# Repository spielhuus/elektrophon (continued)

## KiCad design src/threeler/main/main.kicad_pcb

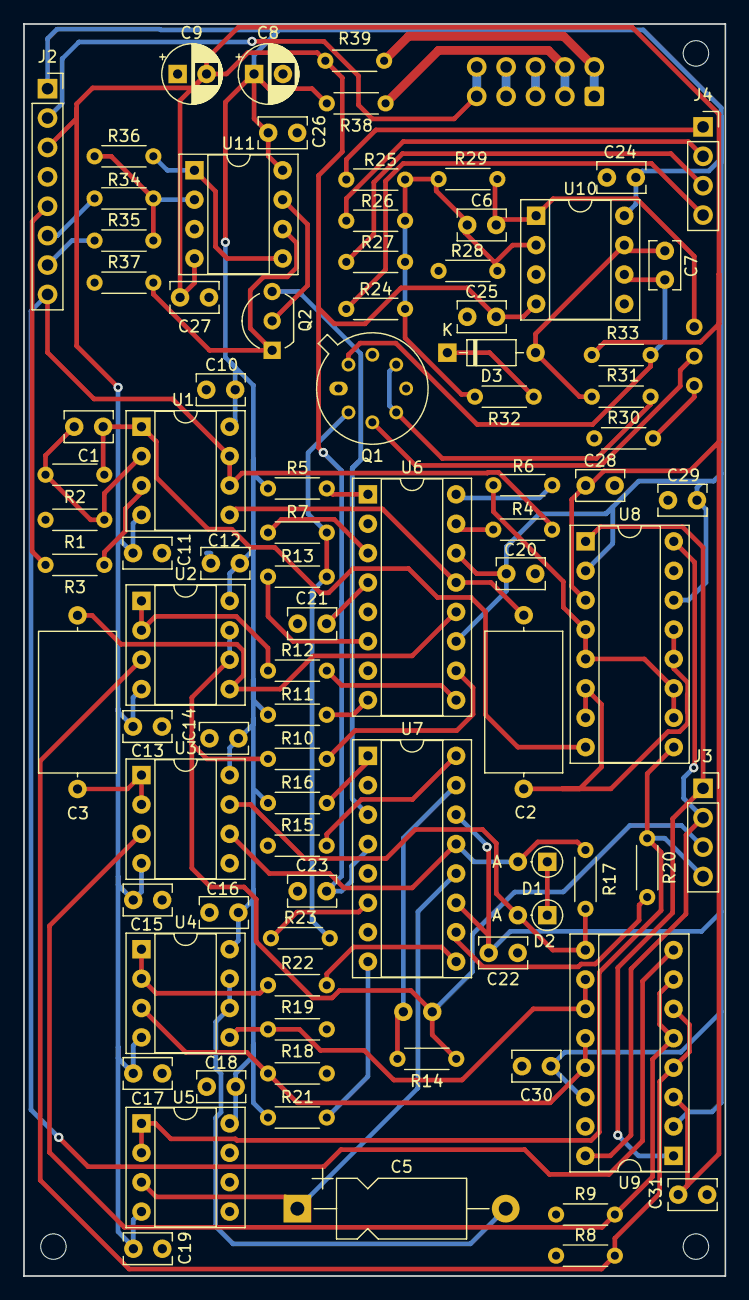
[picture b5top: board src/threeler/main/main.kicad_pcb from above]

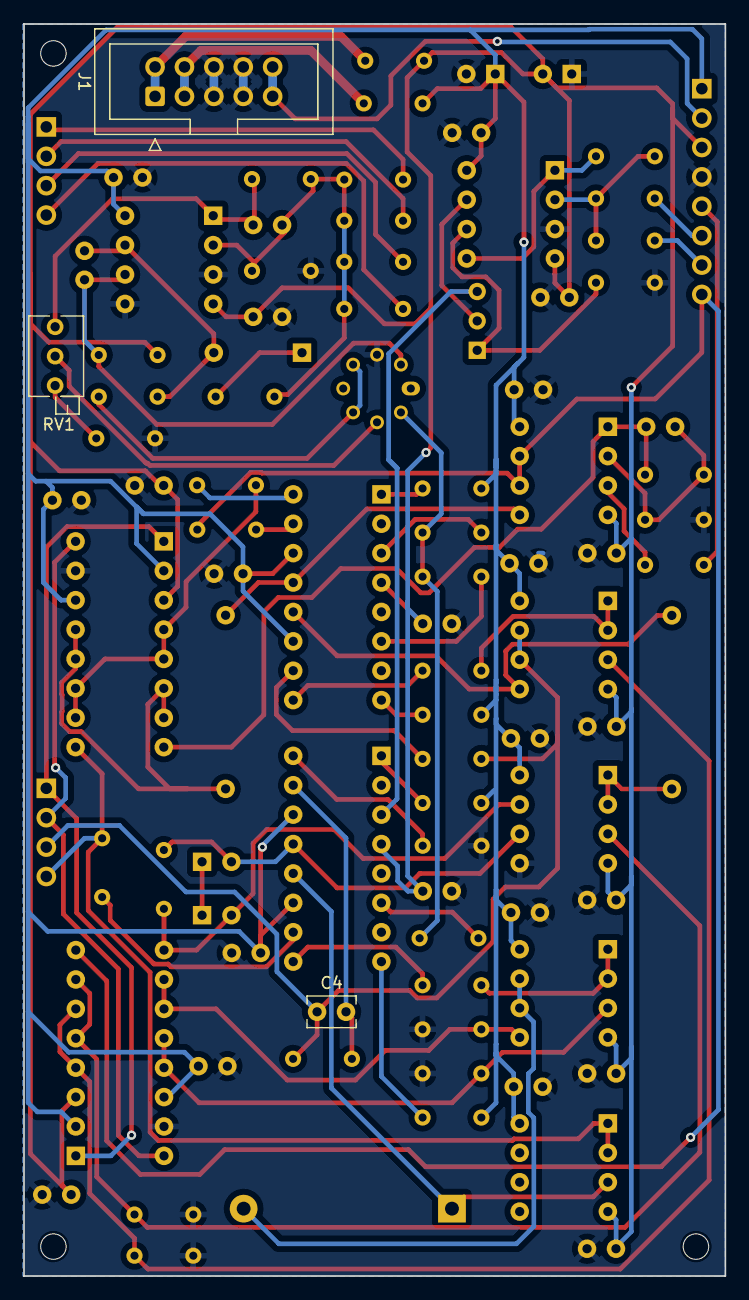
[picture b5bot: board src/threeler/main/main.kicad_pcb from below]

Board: 2 copper layers, 60.6 x 108.2 mm, 94 parts (3 on the bottom side), 66 nets.

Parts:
C1: 56p; C_Rect_L4.0mm_W2.5mm_P2.50mm
C2, C3: 220p; C_Axial_L12.0mm_D6.5mm_P15.00mm_Horizontal
C4: 470p; C_Rect_L4.0mm_W2.5mm_P2.50mm
C5: 220p; CP_Axial_L11.0mm_D5.0mm_P18.00mm_Horizontal
C6, C7: 180p; C_Rect_L4.0mm_W2.5mm_P2.50mm
C8, C9: 10u; CP_Radial_D5.0mm_P2.50mm
C10, C11, C12, C13, C14, C15, C16, C17, C18, C19, C20, C21, C22, C23, C24, C25, C26, C27, C28, C29, C30, C31: 100n; C_Rect_L4.0mm_W2.5mm_P2.50mm
D1, D2: 1N5236; D_DO-35_SOD27_P2.54mm_Vertical_AnodeUp
D3: 1N4148; D_DO-35_SOD27_P7.62mm_Horizontal
H2, H3, H4: MountingHole; MountingHole_2.2mm_M2
J1: IDC_Header; IDC-Header_2x05_P2.54mm_Vertical
J2: Connector; PinSocket_1x08_P2.54mm_Vertical
J3, J4: Connector; PinSocket_1x04_P2.54mm_Vertical
Q1: AS395; TO-5-8
Q2: 2N3906; TO-92_Inline_Wide
R1, R26, R36: 100k; R_Axial_DIN0204_L3.6mm_D1.6mm_P5.08mm_Horizontal
R2: 33k; R_Axial_DIN0204_L3.6mm_D1.6mm_P5.08mm_Horizontal
R3, R4, R6, R10, R12, R14, R15, R20, R22: 22k; R_Axial_DIN0204_L3.6mm_D1.6mm_P5.08mm_Horizontal
R5, R11, R16, R21: 68k; R_Axial_DIN0204_L3.6mm_D1.6mm_P5.08mm_Horizontal
R7, R13, R23, R37: 18k; R_Axial_DIN0204_L3.6mm_D1.6mm_P5.08mm_Horizontal
R8, R9, R18, R19: 5.6k; R_Axial_DIN0204_L3.6mm_D1.6mm_P5.08mm_Horizontal
R17: 220k; R_Axial_DIN0204_L3.6mm_D1.6mm_P5.08mm_Horizontal
R24, R34: 120k; R_Axial_DIN0204_L3.6mm_D1.6mm_P5.08mm_Horizontal
R25: 2.2meg; R_Axial_DIN0204_L3.6mm_D1.6mm_P5.08mm_Horizontal
R27: 150k; R_Axial_DIN0204_L3.6mm_D1.6mm_P5.08mm_Horizontal
R28: 270k; R_Axial_DIN0204_L3.6mm_D1.6mm_P5.08mm_Horizontal
R29: 2k; R_Axial_DIN0204_L3.6mm_D1.6mm_P5.08mm_Horizontal
R30: 330; R_Axial_DIN0204_L3.6mm_D1.6mm_P5.08mm_Horizontal
R31: 3.3k; R_Axial_DIN0204_L3.6mm_D1.6mm_P5.08mm_Horizontal
R32: 1meg; R_Axial_DIN0204_L3.6mm_D1.6mm_P5.08mm_Horizontal
R33: 330k; R_Axial_DIN0204_L3.6mm_D1.6mm_P5.08mm_Horizontal
R35: 100; R_Axial_DIN0204_L3.6mm_D1.6mm_P5.08mm_Horizontal
R38, R39: 10; R_Axial_DIN0204_L3.6mm_D1.6mm_P5.08mm_Horizontal
RV1: 100; Potentiometer_Bourns_3266Z_Horizontal
U1, U2, U3, U4, U5, U10, U11: OPA2134; DIP-8_W7.62mm_Socket
U6, U7: AS3280; DIP-16_W7.62mm_Socket
U8, U9: DG409; DIP-16_W7.62mm_Socket

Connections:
+5V: J1.9, J1.10, J2.2
+15V: C8.1, C10.1, C12.1, C14.1, C16.1, C18.1, C20.1, C22.1, C24.1, C26.1, C29.1, C30.1, J2.1, R5.2, R11.2, R16.2, R21.2, R38.2, U1.8 (V+), U2.8 (V+), U3.8 (V+), U4.8 (V+), U5.8 (V+), U6.11 (V+), U6.14 (V+), U7.11 (V+), U7.14 (V+), U8.2 (EN), U8.14, U9.2 (EN), U9.14, U10.8 (V+), U11.8 (V+)
-15V: C9.2, C11.2, C13.2, C15.2, C17.2, C19.2, C21.2, C23.2, C25.2, C27.2, C28.1, C31.1, J2.3, R33.2, R39.1, U1.4 (V-), U2.4 (V-), U3.4 (V-), U4.4 (V-), U5.4 (V-), U6.4 (V-), U7.4 (V-), U8.3, U9.3, U10.4 (V-), U11.4 (V-)
/A: Q1.2 (E), R7.2, R13.2, R23.2
/A0: J3.1, U8.1 (A0), U9.1 (A0)
/A1: J3.2, U8.16 (A1), U9.16 (A1)
/B: Q2.3 (C), U7.3
/COARSE: J4.4, R24.1
/FINE: J4.1, R25.2
/FM: J4.3, R27.2
/IN: J2.5, R3.2
/OUT_1: J2.8, R4.2, U1.6 (-), U1.7, U9.8
/OUT_2: C4.1, J3.3, R10.2, R14.1, U2.6 (-), U2.7
/OUT_3: J3.4, R20.1, U5.1, U5.2 (-), U8.9
/RES: J2.6, R34.1
/RES_MOD: J2.7, R35.2
/VN: J1.1, J1.2, R39.2
/VP: J1.3, J1.4, R38.1
/V/O: J4.2, R26.2
GND: C8.2, C9.1, C10.2, C11.1, C12.2, C13.1, C14.2, C15.1, C16.2, C17.1, C18.2, C19.1, C20.2, C21.1, C22.2, C23.1, C24.2, C25.1, C26.2, C27.1, C28.2, C29.2, C30.2, C31.2, J1.5, J1.6, J1.7, J1.8, J2.4, Q1.7 (B), R1.2, R8.2, R9.2, R15.2, R18.2, R19.2, R28.2, R30.2, R37.2, U3.5 (+), U8.15 (GND), U9.15 (GND), U10.3 (+), U10.5 (+), U11.3 (+)
unnamed: C1.1, R2.1, U1.1, U8.8
unnamed: C2.2, U8.6, U8.7, U8.12, U8.13
unnamed: C6.1, R29.1, RV1.1, U10.1
unnamed: D1.2 (A), R17.2, U3.6 (-), U7.13
unnamed: D1.1 (K), D2.1 (K)
unnamed: D2.2 (A), R17.1, U3.7, U9.9
unnamed: C7.2, D3.2 (A), R31.1, U10.7
unnamed: D3.1 (K), R32.1
unnamed: Q1.3 (B), RV1.2
unnamed: Q1.4 (C), Q1.6 (C), R31.2
unnamed: C7.1, Q1.8 (E), R33.1, U10.6 (-)
unnamed: Q2.2 (B), U11.7
unnamed: Q2.1 (E), R37.1, U11.6 (-)
unnamed: R6.1, U8.4, U8.5, U8.10, U8.11
unnamed: R7.1, U6.3
unnamed: R13.1, U6.6
unnamed: R23.1, U7.6
unnamed: R30.1, RV1.3
unnamed: R3.1, U1.3 (+)
unnamed: C1.2, R1.1, R2.2, U1.2 (-)
unnamed: C2.1, U1.5 (+), U6.13
unnamed: R8.1, U2.3 (+), U9.4, U9.6
unnamed: R12.1, U2.1, U2.2 (-)
unnamed: C3.1, U2.5 (+), U6.12
unnamed: R9.1, U3.3 (+), U9.5, U9.7
unnamed: C3.2, U3.1, U3.2 (-)
unnamed: R18.1, U4.3 (+), U9.12, U9.13
unnamed: R22.1, U4.1, U4.2 (-)
unnamed: R19.1, U4.5 (+), U9.10, U9.11
unnamed: C5.2, U4.6 (-), U4.7
unnamed: C5.1, U5.3 (+), U7.12
unnamed: R6.2, U6.16 (+)
unnamed: R4.1, U6.15 (-)
unnamed: R5.1, U6.1 (ID)
unnamed: R12.2, U6.9 (+)
unnamed: R10.1, U6.10 (-)
unnamed: R11.1, U6.8 (ID)
unnamed: R15.1, U7.16 (+)
unnamed: C4.2, R14.2, U7.15 (-)
unnamed: R16.1, U7.1 (ID)
unnamed: R22.2, U7.9 (+)
unnamed: R20.2, U7.10 (-)
unnamed: R21.1, U7.8 (ID)
unnamed: C6.2, R24.2, R25.1, R26.1, R27.1, R28.1, R29.2, R32.2, U10.2 (-)
unnamed: R34.2, R35.1, R36.2, U11.2 (-)
unnamed: R36.1, U11.1, U11.5 (+)

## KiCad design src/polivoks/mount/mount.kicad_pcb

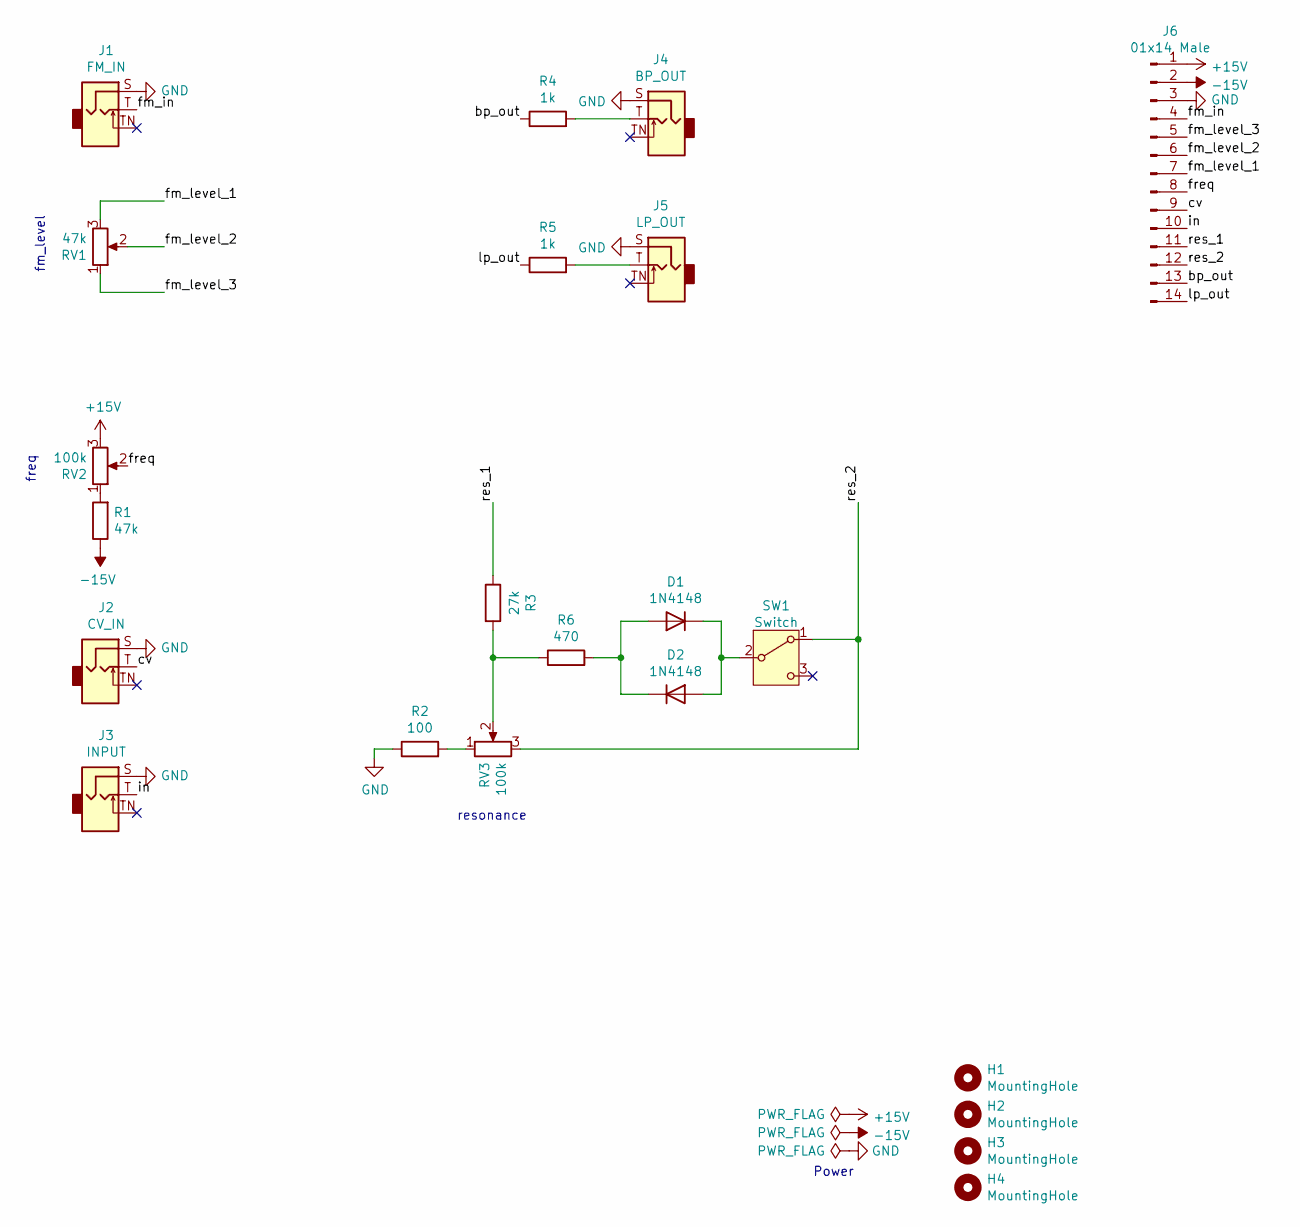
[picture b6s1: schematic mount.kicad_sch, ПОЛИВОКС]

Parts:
D1, D2: 1N4148; D_DO-35_SOD27_P7.62mm_Horizontal
H1, H2, H3, H4: MountingHole; MountingHole_2.2mm_M2
J1: FM_IN; Jack_3.5mm_WQP-PJ398SM_Vertical
J2: CV_IN; Jack_3.5mm_WQP-PJ398SM_Vertical
J3: INPUT; Jack_3.5mm_WQP-PJ398SM_Vertical
J4: BP_OUT; Jack_3.5mm_WQP-PJ398SM_Vertical
J5: LP_OUT; Jack_3.5mm_WQP-PJ398SM_Vertical
J6: 01x14 Male; PinHeader_1x14_P2.54mm_Vertical
R1: 47k; R_Axial_DIN0207_L6.3mm_D2.5mm_P10.16mm_Horizontal
R2: 100; R_Axial_DIN0207_L6.3mm_D2.5mm_P10.16mm_Horizontal
R3: 27k; R_Axial_DIN0207_L6.3mm_D2.5mm_P10.16mm_Horizontal
R4, R5: 1k; R_Axial_DIN0207_L6.3mm_D2.5mm_P10.16mm_Horizontal
R6: 470; R_Axial_DIN0207_L6.3mm_D2.5mm_P10.16mm_Horizontal
RV1: 47k; Potentiometer_Alpha_RD901F-40-00D_Single_Vertical
RV2, RV3: 100k; Potentiometer_Alpha_RD901F-40-00D_Single_Vertical
SW1: Switch; SPDT_KIT

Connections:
+15V: J6.1, RV2.3
-15V: J6.2, R1.1
/bp_out: J6.13, R4.1
/cv: J2.T, J6.9
/fm_in: J1.T, J6.4
/fm_level_1: J6.7, RV1.3
/fm_level_2: J6.6, RV1.2
/fm_level_3: J6.5, RV1.1
/freq: J6.8, RV2.2
/in: J3.T, J6.10
/lp_out: J6.14, R5.1
/res_1: J6.11, R3.1
/res_2: J6.12, RV3.3, SW1.1 (A)
GND: J1.S, J2.S, J3.S, J4.S, J5.S, J6.3, R2.1
unnamed: D1.2 (A), D2.1 (K), R6.2
unnamed: D1.1 (K), D2.2 (A), SW1.2 (B)
unnamed: J4.T, R4.2
unnamed: J5.T, R5.2
unnamed: R1.2, RV2.1
unnamed: R2.2, RV3.1
unnamed: R3.2, R6.1, RV3.2

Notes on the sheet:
fm_level
Power
freq
resonance

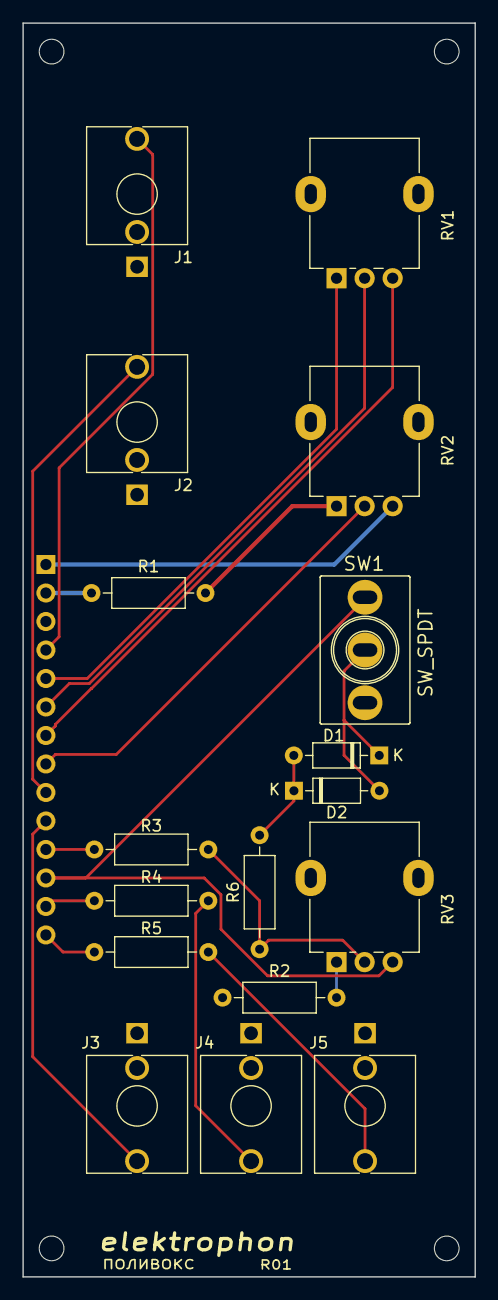
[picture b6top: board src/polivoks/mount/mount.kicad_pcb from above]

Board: 2 copper layers, 40.3 x 111.8 mm, 22 parts (1 on the bottom side), 21 nets.

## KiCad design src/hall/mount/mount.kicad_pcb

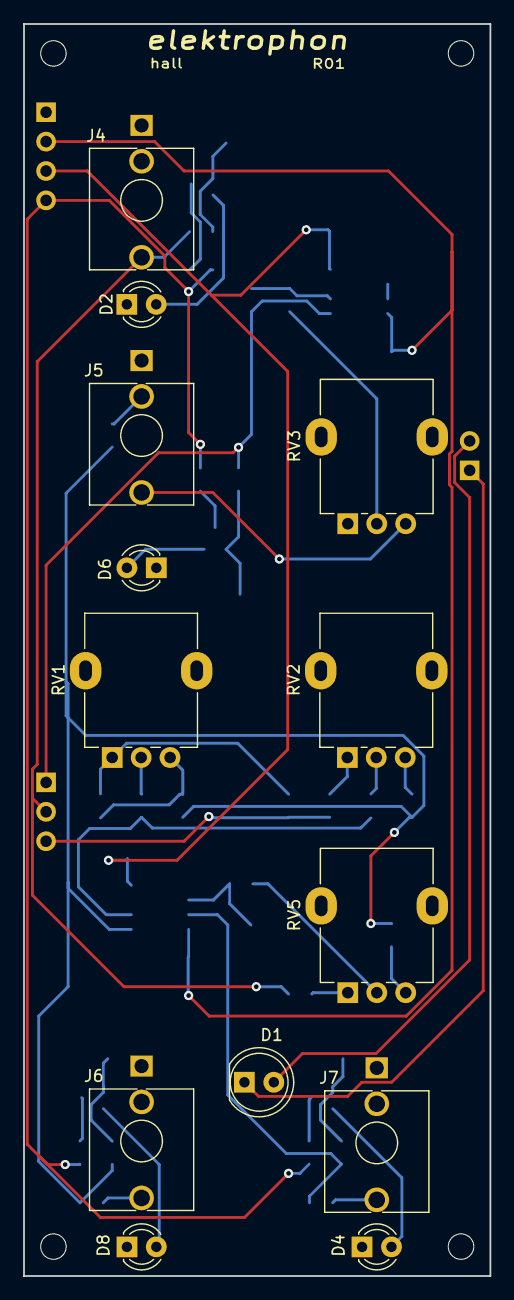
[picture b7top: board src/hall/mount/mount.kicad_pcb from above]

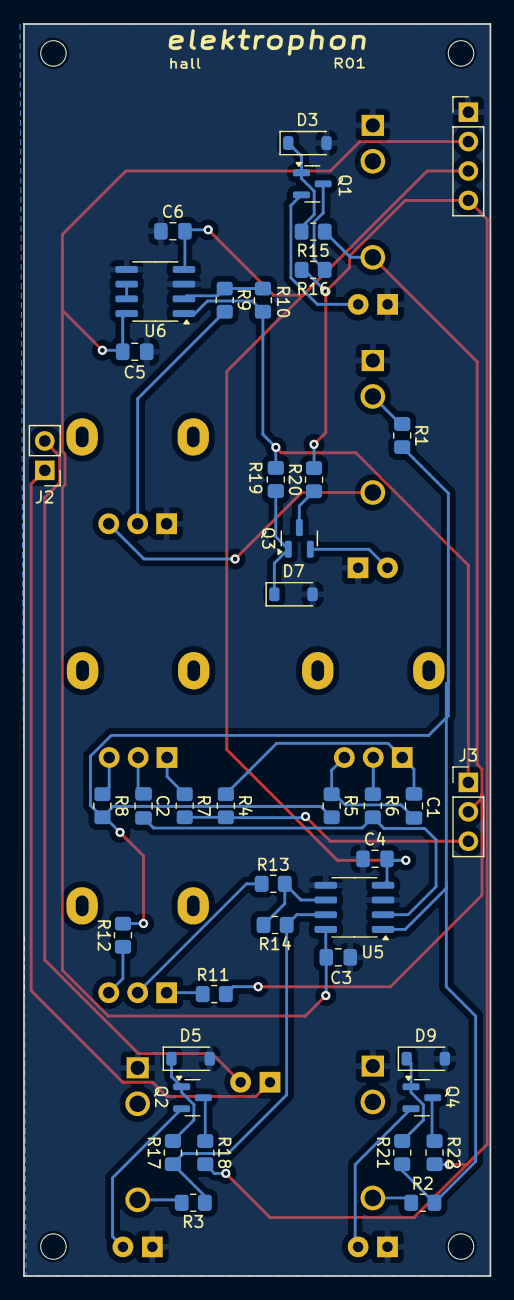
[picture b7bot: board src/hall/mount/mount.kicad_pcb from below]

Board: 2 copper layers, 40.3 x 108.2 mm, 58 parts (41 on the bottom side), 41 nets.

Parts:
C1: 47n (C0G); C_0805_2012Metric_Pad1.18x1.45mm_HandSolder
C2: 560p (C0G); C_0805_2012Metric_Pad1.18x1.45mm_HandSolder
C3, C4, C5, C6: 100n; C_0805_2012Metric_Pad1.18x1.45mm_HandSolder
D1: LED (Red); LED_D5.0mm
D2, D6: LED (Green); LED_D3.0mm
D3, D5, D7, D9: 1N4148W; D_SOD-123
D4, D8: LED (Red); LED_D3.0mm
H1: H1; MountingHole_2.2mm_M2
H2: H2; MountingHole_2.2mm_M2
H3: H3; MountingHole_2.2mm_M2
H4: H4; MountingHole_2.2mm_M2
J1: 01x04 Male; PinHeader_1x04_P2.54mm_Vertical
J2: 01x02 Male; PinHeader_1x02_P2.54mm_Vertical
J3: 01x03 Male; PinHeader_1x03_P2.54mm_Vertical
J4, J5, J6, J7: PJ398SM; Jack_3.5mm_WQP-PJ398SM_Vertical
Q1, Q2, Q3, Q4: MMBT3904; SOT-23
R1, R2, R3: 1k; R_0805_2012Metric_Pad1.20x1.40mm_HandSolder
R4, R5, R6: 22k; R_0805_2012Metric_Pad1.20x1.40mm_HandSolder
R7, R8, R11, R12: 10k; R_0805_2012Metric_Pad1.20x1.40mm_HandSolder
R9, R10, R13, R14, R15, R17, R19, R21: 100k; R_0805_2012Metric_Pad1.20x1.40mm_HandSolder
R16, R18, R20, R22: 5.1k; R_0805_2012Metric_Pad1.20x1.40mm_HandSolder
RV1, RV2, RV3, RV5: 100k; Potentiometer_Alpha_RD901F-40-00D_Single_Vertical
U5, U6: TL072; SOIC-8_3.9x4.9mm_P1.27mm

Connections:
+5V: J1.4, R16.2, R18.2, R20.2, R22.2
+15V: C3.1, C5.1, J1.2, U5.8 (V+), U6.8 (V+)
-15V: C4.2, C6.2, J1.3, U5.4 (V-), U6.4 (V-)
/FB1: R9.1, RV3.2
/FB2: J3.1, R10.1, R19.1, U6.1
/IN: J3.2, J4.T, R11.1, R15.1
/LED1: D1.1 (K), J2.1
/LED2: D1.2 (A), J2.2
/OUT: R3.1, R14.1, R17.1, U5.7
/REVERB: J3.3, R4.1, R7.2
/TONE: R1.2, R2.2, R5.2, R8.2, R12.2, R21.1, U5.1
GND: C3.2, C4.1, C5.2, C6.1, D2.1 (K), D3.2 (A), D4.1 (K), D5.2 (A), D6.1 (K), D7.2 (A), D8.1 (K), D9.2 (A), J1.1, J4.S, J5.S, J6.S, J7.S, RV3.1, U5.3 (+), U5.5 (+), U6.3 (+), U6.5 (+)
unnamed: C1.1, R5.1, RV1.3
unnamed: C1.2, R4.2, RV1.1
unnamed: C2.2, RV2.2
unnamed: D2.2 (A), Q1.2 (E)
unnamed: D3.1 (K), Q1.1 (B), R15.2
unnamed: D4.2 (A), Q2.2 (E)
unnamed: D5.1 (K), Q2.1 (B), R17.2
unnamed: D6.2 (A), Q3.2 (E)
unnamed: D7.1 (K), Q3.1 (B), R19.2
unnamed: D8.2 (A), Q4.2 (E)
unnamed: D9.1 (K), Q4.1 (B), R21.2
unnamed: J5.T, RV3.3
unnamed: J5.TN, R1.1
unnamed: J6.T, R2.1
unnamed: J7.T, R3.2
unnamed: Q1.3 (C), R16.1
unnamed: Q2.3 (C), R18.1
unnamed: Q3.3 (C), R20.1
unnamed: Q4.3 (C), R22.1
unnamed: R6.1, RV1.2
unnamed: R7.1, RV2.1
unnamed: R8.1, RV2.3
unnamed: R11.2, RV5.1
unnamed: R12.1, RV5.3
unnamed: R13.1, RV5.2
unnamed: C2.1, R6.2, U5.2 (-)
unnamed: R13.2, R14.2, U5.6 (-)
unnamed: R9.2, R10.2, U6.2 (-)
unnamed: U6.6 (-), U6.7

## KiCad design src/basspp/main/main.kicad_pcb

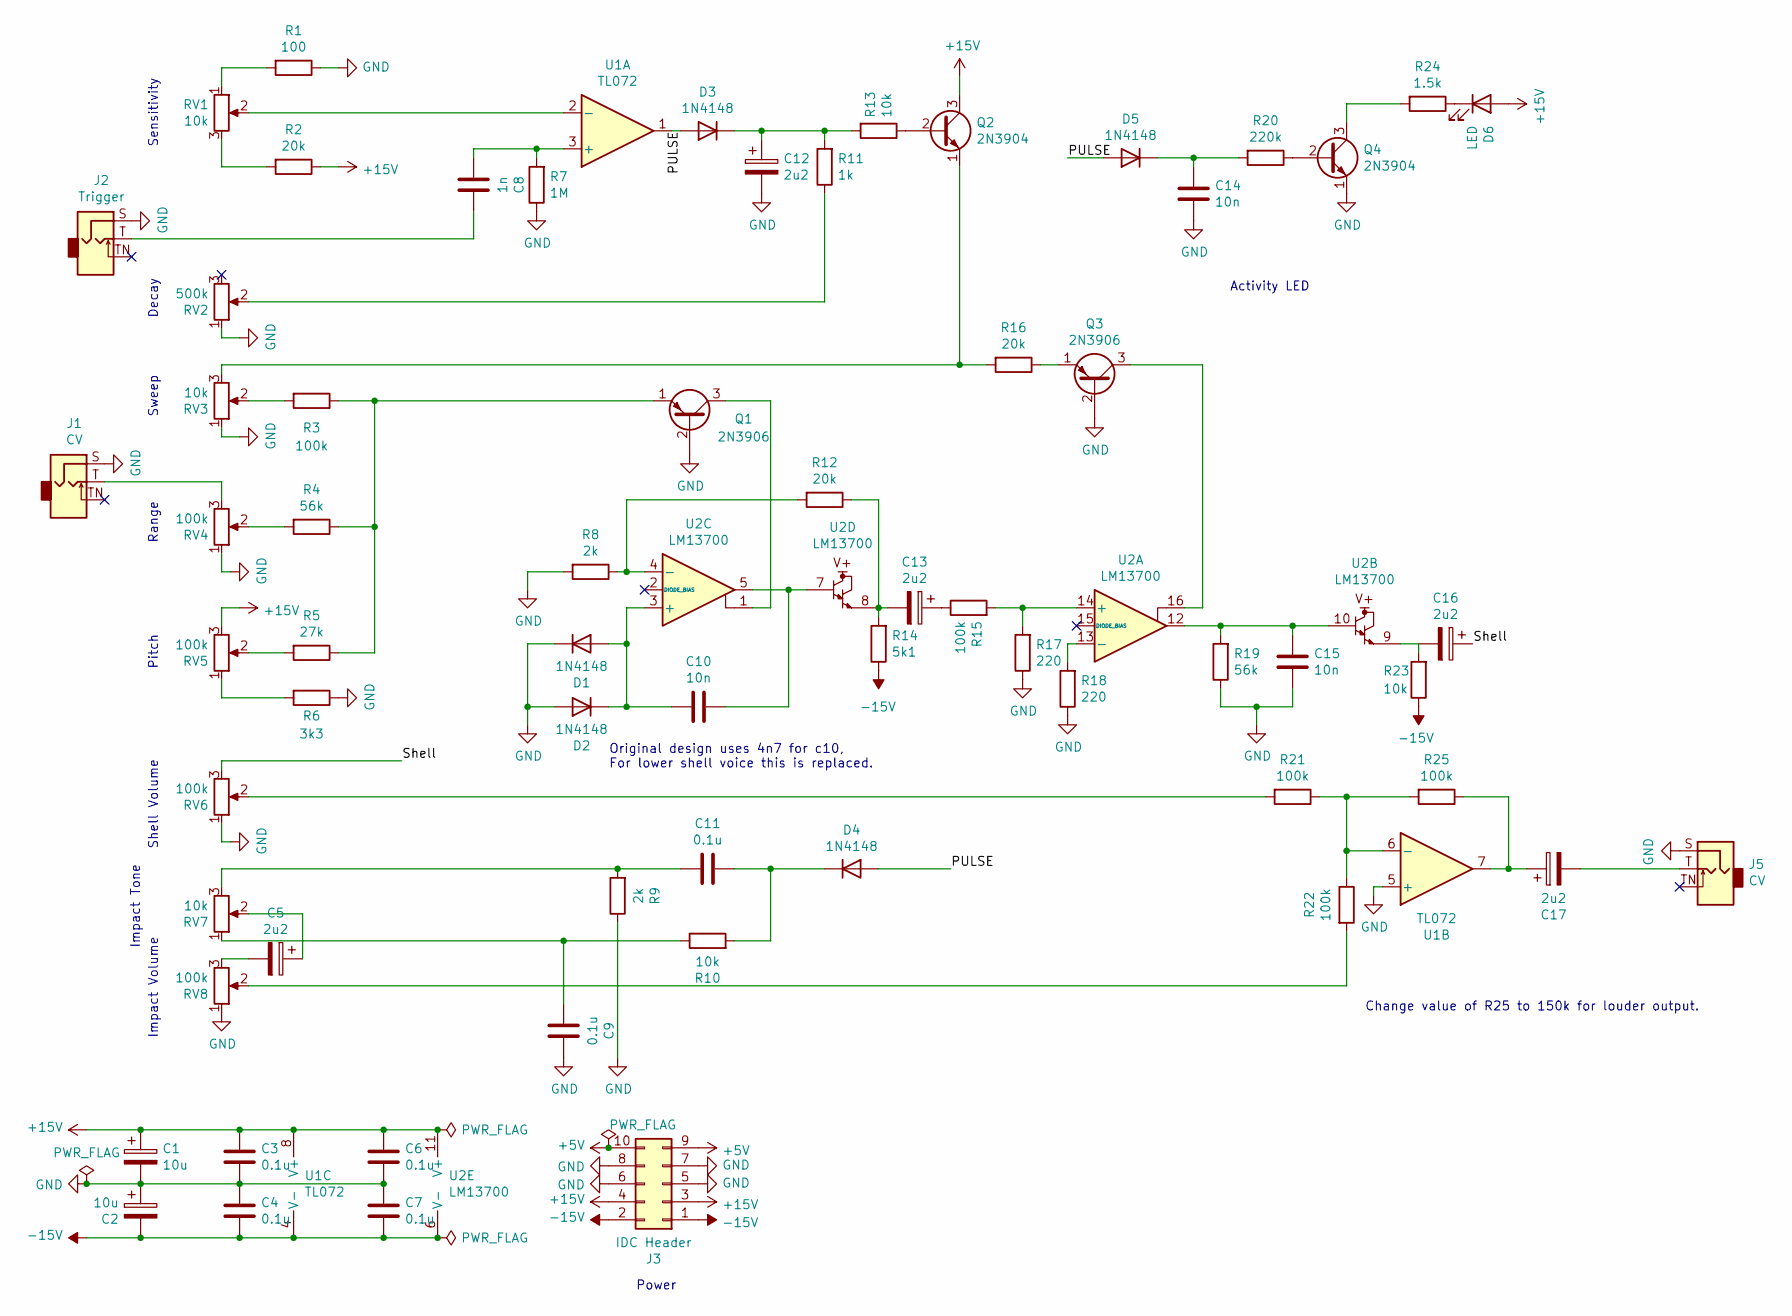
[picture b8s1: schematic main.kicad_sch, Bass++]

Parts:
C1, C2: 10u; CP_Radial_D5.0mm_P2.50mm
C3, C4, C6, C7, C9, C11: 0.1u; C_Disc_D3.4mm_W2.1mm_P2.50mm
C5, C12, C13, C16, C17: 2u2; C_Rect_L7.2mm_W5.5mm_P5.00mm_FKS2_FKP2_MKS2_MKP2
C8: 1n; C_Disc_D3.4mm_W2.1mm_P2.50mm
C10, C14, C15: 10n; C_Disc_D3.4mm_W2.1mm_P2.50mm
D1, D2, D3, D4, D5: 1N4148; D_DO-35_SOD27_P7.62mm_Horizontal
D6: LED; LED_D5.0mm
J1, J5: CV; Jack_3.5mm_QingPu_WQP-PJ398SM_Vertical_CircularHoles
J2: Trigger; Jack_3.5mm_QingPu_WQP-PJ398SM_Vertical_CircularHoles
J3: IDC Header; IDC-Header_2x05_P2.54mm_Vertical
Q1, Q3: 2N3906; TO-92_Inline
Q2, Q4: 2N3904; TO-92_Inline
R1: 100; R_Axial_DIN0207_L6.3mm_D2.5mm_P10.16mm_Horizontal
R2, R12, R16: 20k; R_Axial_DIN0207_L6.3mm_D2.5mm_P10.16mm_Horizontal
R3, R15, R21, R22, R25: 100k; R_Axial_DIN0207_L6.3mm_D2.5mm_P10.16mm_Horizontal
R4, R19: 56k; R_Axial_DIN0207_L6.3mm_D2.5mm_P10.16mm_Horizontal
R5: 27k; R_Axial_DIN0207_L6.3mm_D2.5mm_P10.16mm_Horizontal
R6: 3k3; R_Axial_DIN0207_L6.3mm_D2.5mm_P10.16mm_Horizontal
R7: 1M; R_Axial_DIN0207_L6.3mm_D2.5mm_P10.16mm_Horizontal
R8, R9: 2k; R_Axial_DIN0207_L6.3mm_D2.5mm_P10.16mm_Horizontal
R10, R13, R23: 10k; R_Axial_DIN0207_L6.3mm_D2.5mm_P10.16mm_Horizontal
R11: 1k; R_Axial_DIN0207_L6.3mm_D2.5mm_P10.16mm_Horizontal
R14: 5k1; R_Axial_DIN0207_L6.3mm_D2.5mm_P10.16mm_Horizontal
R17, R18: 220; R_Axial_DIN0207_L6.3mm_D2.5mm_P10.16mm_Horizontal
R20: 220k; R_Axial_DIN0207_L6.3mm_D2.5mm_P10.16mm_Horizontal
R24: 1.5k; R_Axial_DIN0207_L6.3mm_D2.5mm_P10.16mm_Horizontal
RV1, RV3, RV7: 10k; Potentiometer_Alpha_RD901F-40-00D_Single_Vertical
RV2: 500k; Potentiometer_Alpha_RD901F-40-00D_Single_Vertical
RV4, RV5, RV6, RV8: 100k; Potentiometer_Alpha_RD901F-40-00D_Single_Vertical
U1: TL072; DIP-8_W7.62mm_Socket
U2: LM13700; DIP-16_W7.62mm_Socket

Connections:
+5V: J3.9, J3.10
+15V: C1.1, C3.1, C6.1, D6.2 (A), J3.3, J3.4, Q2.3 (C), R2.1, RV5.3, U1.8 (V+), U2.11 (V+)
-15V: C2.2, C4.2, C7.2, J3.1, J3.2, R14.1, R23.1, U1.4 (V-), U2.6 (V-)
/PULSE: D3.2 (A), D4.2 (A), D5.2 (A), U1.1
/Shell: C16.1, RV6.3
GND: C1.2, C2.1, C3.2, C4.1, C6.2, C7.1, C9.1, C12.2, C14.2, C15.1, D1.1 (K), D2.2 (A), J1.S, J2.S, J3.5, J3.6, J3.7, J3.8, J5.S, Q1.2 (B), Q3.2 (B), Q4.1 (E), R1.1, R6.1, R7.1, R8.2, R9.1, R17.1, R18.1, R19.1, RV2.1, RV3.1, RV4.1, RV6.1, RV8.1, U1.5 (+)
unnamed: C5.1, RV7.2
unnamed: C5.2, RV8.3
unnamed: C8.1, J2.T
unnamed: C9.2, R10.1, RV7.1
unnamed: C10.1, U2.5, U2.7
unnamed: C11.2, R9.2, RV7.3
unnamed: C13.1, R15.1
unnamed: C13.2, R12.1, R14.2, U2.8
unnamed: C15.2, R19.2, U2.10, U2.12
unnamed: C16.2, R23.2, U2.9
unnamed: C17.1, R25.1, U1.7
unnamed: C17.2, J5.T
unnamed: C10.2, D1.2 (A), D2.1 (K), U2.3 (+)
unnamed: C12.1, D3.1 (K), R11.2, R13.2
unnamed: C11.1, D4.1 (K), R10.2
unnamed: C14.1, D5.1 (K), R20.2
unnamed: D6.1 (K), R24.1
unnamed: J1.T, RV4.3
unnamed: Q1.3 (C), U2.1
unnamed: Q1.1 (E), R3.1, R4.1, R5.1
unnamed: Q2.2 (B), R13.1
unnamed: Q2.1 (E), R16.2, RV3.3
unnamed: Q3.3 (C), U2.16
unnamed: Q3.1 (E), R16.1
unnamed: Q4.2 (B), R20.1
unnamed: Q4.3 (C), R24.2
unnamed: R1.2, RV1.1
unnamed: R2.2, RV1.3
unnamed: R3.2, RV3.2
unnamed: R4.2, RV4.2
unnamed: R5.2, RV5.2
unnamed: R6.2, RV5.1
unnamed: R11.1, RV2.2
unnamed: R21.2, RV6.2
unnamed: R22.2, RV8.2
unnamed: C8.2, R7.2, U1.3 (+)
unnamed: RV1.2, U1.2 (-)
unnamed: R21.1, R22.1, R25.2, U1.6 (-)
unnamed: R15.2, R17.2, U2.14 (+)
unnamed: R18.2, U2.13 (-)
unnamed: R8.1, R12.2, U2.4 (-)

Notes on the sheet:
Range
Change value of R25 to 150k for louder output.
Original design uses 4n7 for c10, For lower shell voice this is replaced.
Sweep
Power
Sensitivity
Activity LED
Shell Volume
Impact Volume
Impact Tone
Decay
Pitch

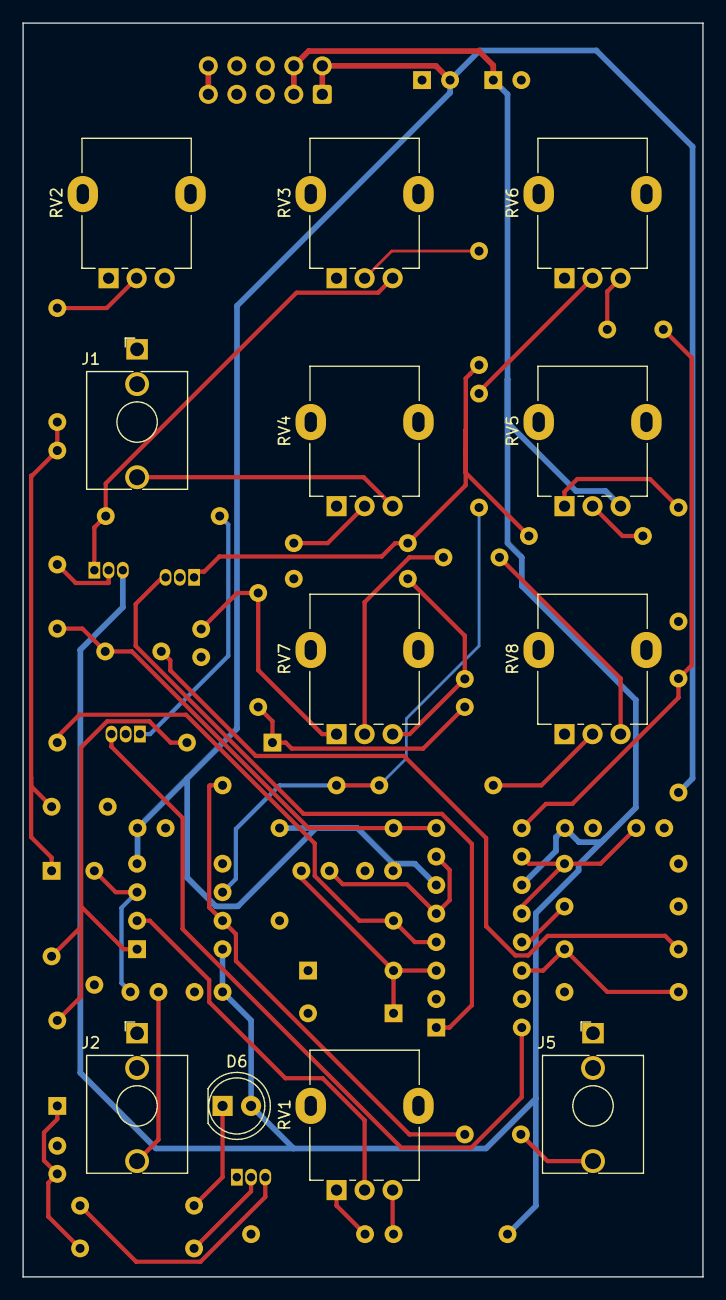
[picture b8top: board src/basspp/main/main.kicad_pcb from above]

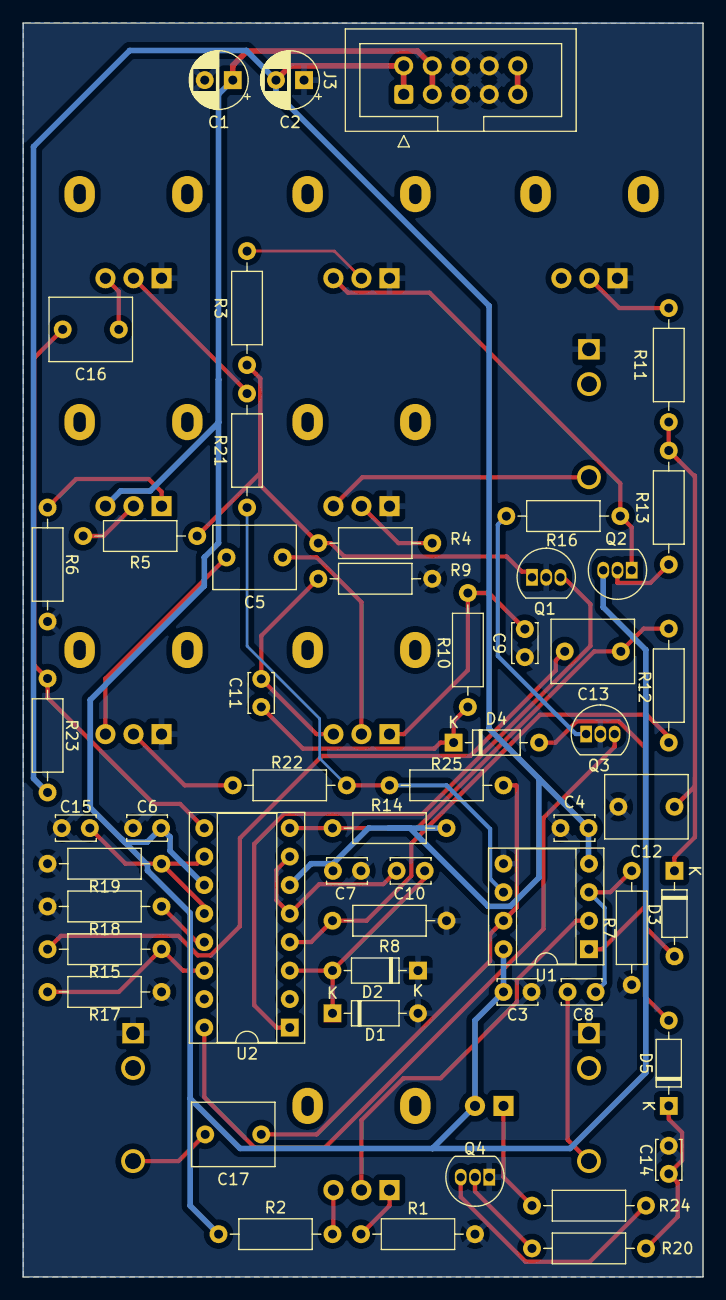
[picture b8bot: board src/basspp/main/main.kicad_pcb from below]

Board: 2 copper layers, 60.6 x 111.8 mm, 66 parts (54 on the bottom side), 47 nets.

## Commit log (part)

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2021-01-02 add summe module
2021-01-03 update dockerfile
2021-01-20 new site sructure
2021-01-20 remove built site
2021-01-20 add dependencies
2021-01-20 update site
2021-01-21 update docker image
2021-01-24 add kicad config
2021-01-24 fix docker batches
2021-01-29 arp filter
2021-01-30 update cmos buffer
2021-01-30 update cmos filter
2021-02-05 add drafts
2021-02-06 update dickerfile
2021-02-06 add codona env
2021-02-07 update binder files
2021-02-07 update conda env
2021-02-07 add README.md
2021-02-07 add github workflow
2021-02-07 add latex
2021-02-07 update project
2021-02-07 update draft projects
2021-02-08 update jekyll pages
2021-02-21 update cmos articles
2021-02-21 update articles
2021-02-21 Initial gh-pages commit
2021-02-21 Deploying to gh-pages from @ 5292d64ad73bc9d8562c1955eff184c9ac001670 🚀
2021-02-23 update content
2021-02-23 Deploying to gh-pages from @ a6751cbd7a6748923aaf881d94088f70f07121df 🚀
2021-02-24 Deploying to gh-pages from @ 4ee9f4b7b9b02af84ed8ab10b2e0071abf18ee7e 🚀
2021-02-25 Deploying to gh-pages from @ 2a4af2e5055915d0c36d5947a37283b7979d01dd 🚀
2021-02-26 Deploying to gh-pages from @ 10bae65a30056d705f80bece5ed3078aed25defd 🚀
2021-03-14 update docker files
2021-03-14 remove images
2021-03-14 remove datasheets
2021-03-14 update kobot parser
2021-03-14 remove old docs
2021-03-27 add ngspice config
2021-03-27 Deploying to gh-pages from @ 4cff0d933f6c5432f52e7934fee5c952c7536f9b 🚀
2021-03-28 add 40106 spice library
2021-03-28 update drafts
2021-03-28 Deploying to gh-pages from @ 57854ea18bd6556fac03f3b007b2a9923a060d47 🚀
2021-03-29 Deploying to gh-pages from @ 046f1f6020a2c98c6e3e69bdc94f9d165074b769 🚀
2021-04-02 add new index file
2021-04-02 update vermarkung
2021-04-03 update header include
2021-04-04 separate make all and deploy calls
2021-04-04 Deploying to gh-pages from @ 27ac4f83dabfe3ab3d65eb5d2f9fc244610cde25 🚀
2021-04-05 update webpage
2021-04-05 add deploy to makefile
2021-04-05 add bom xml files
2021-04-05 change configuration
2021-04-05 Deploying to gh-pages from @ b5879c7718d9f56599e847abe450a053e1b8f028 🚀
2021-05-06 update power supply
2021-05-06 Deploying to gh-pages from @ bc23672b609c0db3e29cba9083c72566656b6efa 🚀
2021-05-15 add kraft
2021-05-15 Deploying to gh-pages from @ 65c586f7e8192ed80d746c9df6b0ae495c1b8012 🚀
2021-05-16 add svg utils
2021-05-16 downgrade ubuntu version
2021-05-17 Deploying to gh-pages from @ 78fcc5c646bf412ab1cb216887b75d8e7cef7501 🚀
2021-05-20 update summe
2021-05-20 Deploying to gh-pages from @ 5a8ff52d898957d2cd98a9c954d9bad597f01ff8 🚀
2021-05-24 add pytest
2021-05-24 Deploying to gh-pages from @ fbb00e17579b5a37a4178a37b20ad467a19c07d5 🚀
2021-05-25 add summe and pegel
2021-05-25 Deploying to gh-pages from @ 8bb06ad505781f4b90717e0c540aa0afbdb588cb 🚀
2021-05-25 add vermarkung files
2021-05-25 Deploying to gh-pages from @ cb460c3f0b42520fb7dec208be4e9a2479a830b0 🚀
2021-06-06 update kraft page
2021-06-06 add kicad templates
2021-06-06 update jekyll page
2021-06-06 Deploying to gh-pages from @ 39ea855c6746256e1a9b9e4a4b9b539c5a125be6 🚀
2021-06-07 update kraft
2021-06-07 update images
2021-06-07 update layout
2021-06-07 add 555 vco
2021-06-07 Deploying to gh-pages from @ 16868ac20f9198cc03514f999c9b9513a6987163 🚀
2021-06-08 update vco
2021-06-08 Deploying to gh-pages from @ 66044c40cc42695cac4fb77306ba74f44b167f50 🚀
2021-06-17 Deploying to gh-pages from @ 5966a026cb0693c0b05be9f7bc89bb8329677972 🚀
2021-06-19 update kraft site
2021-06-19 update pegel site
2021-06-19 update summe site
2021-06-19 update vco pcbe
2021-06-20 update kicad footprints
2021-06-20 add steckfeld
2021-06-21 rename 555 vco
2021-06-21 Deploying to gh-pages from @ ed9a4c0d9a5960544eedf73a6a4862304f59d76a 🚀
2021-06-22 fix pegel
2021-06-22 Deploying to gh-pages from @ 6de8f6fa3f2f021290e2caf5ce714b4458538629 🚀
2021-06-22 Deploying to gh-pages from @ 4245fe0628967fae432e5328fb93a9f3e08a0bd0 🚀
2021-06-25 fix bom
2021-06-25 Deploying to gh-pages from @ 521c271977a9afb41f38aec57bcbf26b2a087d6f 🚀
2021-06-28 update silkscreen
2021-06-28 Deploying to gh-pages from @ 48c058318a0e0a3841eb12d1e45b54c324c9eb3f 🚀
2021-07-05 update to scons build system
2021-07-05 update bulma
2021-07-06 update kicad template
2021-07-06 update jupyter template
2021-07-06 add scons file
2021-07-06 update arbeitsplatz
2021-07-06 update to scons
2021-07-06 update includes
2021-07-06 add scons
2021-07-06 output username
2021-07-06 update jinja template
2021-07-06 Deploying to gh-pages from @ 7bbc16728efc8824c77e5645c330fe7fd8e9ff9a 🚀
2021-07-07 replace pdf2svg
2021-07-07 Deploying to gh-pages from @ 7c834a938373201214570722c6a7ba20910fffc9 🚀
2021-07-08 Deploying to gh-pages from @ ddf4ab0207eff3da4d69caa8d73a109a0285b2a3 🚀
2021-07-12 add oscillator
2021-07-12 Deploying to gh-pages from @ b9813a8a68cf31fd59427452498918dc752729ad 🚀
2021-07-13 update oszillator
2021-07-13 Deploying to gh-pages from @ 1ab0eecc2dbbf681f7e09e748568174165d12a2f 🚀
2021-07-14 update dco calculation
2021-07-14 Deploying to gh-pages from @ 2fc303ff9b5469e3b00d2fa4e50f00ce668ce766 🚀
2021-07-14 add firmware
2021-07-14 Deploying to gh-pages from @ 4c2c3ffb56fb7ef633c16791b81d9379e7a6e1fa 🚀
2021-07-16 add STM32 description
2021-07-16 add lm353
2021-07-16 add equalizer
2021-07-16 add vscode build description
2021-07-16 Deploying to gh-pages from @ ddf8a57747e003a63284da28cf1c2fb6069ed3d6 🚀
2021-07-17 mcp4822 calculation
2021-07-28 add pcb
2021-07-28 fix excerpt
2021-07-28 add produkt
2021-07-28 update stabilizing capcitor
2021-07-28 add capacitor
2021-07-28 Deploying to gh-pages from @ 7b3312314c2217feefd05a60918e375b5cb1eb88 🚀
2021-07-28 change capacitor value
2021-07-28 Deploying to gh-pages from @ 397571aaf24a5927b81d1a0165102c8c82a511c6 🚀
2021-07-29 python dependency to junit xml
2021-07-29 Deploying to gh-pages from @ 5aef9196b7f8ce3bc0a0005b0787cf4128c45e90 🚀
2021-07-30 update libraries
2021-07-30 update pcb
2021-07-30 Deploying to gh-pages from @ c7be6f036143e16472f1901002e967f141e6913b 🚀
2021-07-30 create junit compatible test report
2021-07-30 Deploying to gh-pages from @ 10c6690f581b6e3f7d19969d6ab043e7180a136e 🚀
2021-07-30 Deploying to gh-pages from @ 58a44678837f05b25430cc1ac3bcbb81dba6d053 🚀
2021-07-30 Deploying to gh-pages from @ 1d3330ab5f8f4219578e50c5ccaced029c8c9b4c 🚀
2021-07-30 Deploying to gh-pages from @ e1d4699a8072d778c7b88ac894a67a5d8054f345 🚀
2021-07-30 Deploying to gh-pages from @ 0b7dd546c911bbedaf623e4043329e139a1e6634 🚀
2021-07-30 update PCB's
2021-07-30 Deploying to gh-pages from @ 8cba5c350744e3cf42ce03136c4c270a6c2e764e 🚀
2021-07-31 update main PCB
2021-07-31 Deploying to gh-pages from @ 8c39442373227b380ae98dffadbb7aa548c31a82 🚀
2021-07-31 update hero
2021-07-31 update kicad config
2021-07-31 update kicad config files
2021-07-31 Deploying to gh-pages from @ 5d6d0afdb5b83ffa3547c4b4ef9c373bdd6d1d40 🚀
2021-07-31 Deploying to gh-pages from @ 26bf25d58a88d19ad5c801f7140ac1c0ed35a234 🚀
2021-08-01 finalize pcb
2021-08-01 Deploying to gh-pages from @ 1c7a3b2a6f7dd8120c74ec4a4cb2c3826cb399d0 🚀
2021-08-04 change to chart.js
2021-08-04 update bom
2021-08-04 add draft option for build
2021-08-04 add js output to html template
2021-08-04 version update
2021-08-04 Deploying to gh-pages from @ fa12ba0902af8c54d31018f71d3e2026c5dbad9b 🚀
2021-08-06 Deploying to gh-pages from @ 12bc2cad93db129c1fcdfcf72b969c07155f0431 🚀
2021-08-09 add cv calculation
2021-08-09 Deploying to gh-pages from @ de8f2313f0be91926615d15d822d45d6a269c6ad 🚀
2021-08-11 Deploying to gh-pages from @ cc4b6eb38ddaa59b21d06ed501573d49b2c15cd0 🚀
2021-08-14 tiefpass initial commit
2021-08-14 update kicad library
2021-08-14 Deploying to gh-pages from @ cc8555e154e447037f93fe9c3a7d825538039290 🚀
2021-08-19 output markdown and latex
2021-08-19 add 3PDT switch
2021-08-19 Deploying to gh-pages from @ b8fec85995a3ce37a4b8a13dd459b526f50f74c4 🚀
2021-08-27 add documentation
2021-08-27 add TL074 spice lib
2021-08-27 Deploying to gh-pages from @ 89e712d0359dcdaff211eb78488505a92f5a9395 🚀
2021-08-29 add spring reverb
2021-08-29 Deploying to gh-pages from @ 9450cedb7bcd100ea4228507b6fd08147a2371af 🚀
2021-09-04 add cmos notebooks
2021-09-04 Deploying to gh-pages from @ de9ae7110ed5e2d2ea52fe11b42f05355aa2ecc6 🚀
2021-09-05 add reverb notebook
2021-09-05 Deploying to gh-pages from @ 5ffc76ed07185098872ce633dc2b7e198b4de27d 🚀
2021-09-11 update notebooks
2021-09-11 Deploying to gh-pages from @ acab36e7442958c6faa96947d2eb6f1514529e68 🚀
2021-09-12 add dds article
2021-09-12 Deploying to gh-pages from @ 8c3e33d5ea018994556e135164bd405221a3d851 🚀
2021-09-25 update echo
2021-10-02 add ian fritz AD/AR
2021-10-03 update documentation
2021-10-03 update envelope
2021-10-03 add vca
2021-10-03 add 555, 2n3906 and CD4007 spice model
2021-10-03 Deploying to gh-pages from @ 234b8043165043d88d28151d80153f07ecd5e8d0 🚀
2021-10-04 add new modules
2021-10-04 update sconstruct
2021-10-05 Deploying to gh-pages from @ 4233999145a0b5b895b5055aab9a486785dec8c6 🚀
2021-10-14 add ad/ar schematics
2021-10-14 Deploying to gh-pages from @ d9c456f779d402b5738cb1793cfe74d58beaf806 🚀
2021-10-16 update symbols
2021-10-16 Deploying to gh-pages from @ e5a77b23bb107b62cf48070b30c1c79598db50c3 🚀
2021-10-18 add panel
2021-11-07 refactor to hugo site generator
2021-11-10 Update README.md
    https://forum.kicad.info/t/warning-avoid-all-links-to-kicad-pcb-org-use-kicad-org/31521
2021-11-15 remove old files
2021-11-15 rename www folder
2021-11-16 update user entrypoint
2021-11-20 update files
2021-11-21 Deploying to gh-pages from @ 42fc17a0a3787c31a8f0e530dc1b25731e533bfa 🚀
2021-11-21 update drc report
2021-11-21 add minify option
2021-11-21 Deploying to gh-pages from @ b4759578d3601b37786598d2e712700a719eb979 🚀
2021-11-24 cleanup files
2021-12-04 Deploying to gh-pages from @ afd4c9c84c6ef2571264b1e24c49a9609f847bf5 🚀
2021-12-04 Deploying to gh-pages from @ 3ca0650f4846b73f5b8783a32f913be7a6ad6cac 🚀
2021-12-05 css url
2021-12-05 Deploying to gh-pages from @ 2bf8f49e1d8184df97b29f995c2fef5540f52301 🚀
2021-12-05 make rel path
2021-12-05 Deploying to gh-pages from @ 3af8e6658a60dd2ecde5af0ef7e6ab26032331ac 🚀
2021-12-05 update web template
2021-12-05 Deploying to gh-pages from @ 183b5722406378b675c33d81b42170e2cfe315f3 🚀
2021-12-05 Create CNAME
2021-12-05 Deploying to gh-pages from @ 8e59f93285e8700f7d48b61a3b8a4fc05cfcdd9e 🚀
2021-12-06 Update CNAME
2021-12-07 update web page
2021-12-07 Deploying to gh-pages from @ ce71223b69357baf7c5a8a3f759b314adae81d7b 🚀
2021-12-07 Deploying to gh-pages from @ 3726fafe6bc107237c33020020b30129ef0c44c2 🚀
2021-12-11 summe release 2
2021-12-12 dateformat
2021-12-12 Deploying to gh-pages from @ ae44cea0c1c20a0bce46e29c55107cdc1ec2c6c5 🚀
2021-12-20 update oszillator schema
2021-12-20 update sinus schema
2021-12-20 remove ARP filter
2021-12-20 update pin mapping
2021-12-20 add jfet
2021-12-20 add tl431 voltage regulator
2021-12-20 update content status
2021-12-20 add page warnings for draft modules
2021-12-21 update index page
2021-12-21 Deploying to gh-pages from @ 9b7bb22c6fc3a448ab61864ca8e4ca3fa6c948b1 🚀
2021-12-22 arange silkscreen
2021-12-22 note for opamp for diode
2021-12-22 Deploying to gh-pages from @ ae07c810be4b346c1eec1d190253271adfc8b0c2 🚀
2021-12-23 add images
2021-12-23 Deploying to gh-pages from @ bf8b45dc04ab33e6536e7235c290643d3e1c829e 🚀
2021-12-25 add kicad libraries
2021-12-25 add new libraries
2021-12-26 update schemas
2021-12-26 add google analytics
2021-12-26 add core schema
2021-12-26 Deploying to gh-pages from @ 9a59b314a029efcc2771a4fac9aab9f0b0729c46 🚀
2021-12-26 update google analytics tag
2021-12-26 Deploying to gh-pages from @ 1ef18c005a1ee1ce1f921d3e2babc8601c79cca7 🚀
2021-12-27 update hall, funktion and animation
2021-12-27 update to versioned dockerfile
2021-12-27 Deploying to gh-pages from @ 5431c6ece5f9de926203e5f4ffcdbdd66eaccea4 🚀
2021-12-28 add animation schematics
2021-12-28 Deploying to gh-pages from @ ffbe32eba5d9151585a00b82de1acabfcc52cf3b 🚀
2021-12-29 update schema
2021-12-29 Deploying to gh-pages from @ 4a36f1d070573f8189c2719a08670460c3c1e389 🚀
2021-12-29 transistor pinout
2021-12-29 Deploying to gh-pages from @ 6d9e95f3d685c6de024c4e54bcbfb04837b40df4 🚀
2023-12-23 update with elektron
2024-01-14 add logos and include in site
2024-03-09 update theme
2024-03-24 update to Kicad8
2024-04-07 fix errors in index files
2024-04-12 update elektron theme
